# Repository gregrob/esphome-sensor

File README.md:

# ESPHome Sensor

An ESP32-S3 based sensor board system for ESPHome and Home Assistant, designed for outdoor environmental monitoring with a focus on hot water system and water tank level monitoring. Includes a complete mechanical system with 3D printable parts and a purpose-built outdoor 12V DC power distribution unit.

*Tank Sensor with Adapter*

*Tank Sensor in Operation*

## Features

- ESP32-S3 (FeatherS3D) with WiFi and ESPHome integration
- PiicoDev OLED display for local status indication
- Dual 1-Wire buses for DS18B20 temperature sensors
- I2C expansion for ToF distance sensors (DFRobot SEN0590)
- RGB LED status indicator with gradient colour coding
- Outdoor-rated polycarbonate enclosures with cable glands
- Purpose-built 12V DC zone power distribution unit (PSU backboard)
- 3D printed PETG-HF mechanical components

## Main Hardware Overview

| Component | Description |
|-----------|-------------|
| ESP32-S3 FeatherS3D | Main microcontroller |
| PiicoDev OLED 128x64 | Local display |
| Pololu D24V5F5 | 5V step-down regulator |
| DFRobot SEN0590 | ToF distance sensor |
| DS18B20 | 1-Wire temperature sensors |
| Mean Well IRM-30-12ST | 12V 2.5A AC/DC PSU |

## Documentation

- [Hardware](docs/hardware.md) — PCB design, schematic, BOM, KiCad files
- [Mechanical](docs/mechanical.md) — 3D printing, enclosures, print settings, materials
- [PSU Backboard](docs/esphome-sensor-psu-backboard.md) — Outdoor 12V DC power distribution unit

## Project Structure

```
├── README.md
├── hardware/
│   └── kicad/              # KiCad schematic, PCB, Gerber, BOM
├── mechanical/
│   ├── fusion360/          # Fusion 360 source files (.f3d)
│   ├── exports/            # STL and STEP files for printing
│   └── icons/              # Incons used in the covers
├── datasheets/             # Component datasheets
└── docs/                   # Detailed documentation
    └── images/             # Build photos
```

## Applications

- Heat pump hot water system monitoring (temperature, capacity estimation)
- Rainwater tank level monitoring (ToF distance sensor)
- Outdoor distributed IoT sensor power distribution

## TODO

- [ ] Write `docs/hardware.md`
- [ ] Write `docs/mechanical.md`
- [ ] Better tank sensor demo photo
- [ ] Sync software for ESPHome in personal HA repo here
- [ ] UV rated cables for ToF sensor
- [ ] Finalise tank adaptr
  - [ ] Proper cable mounts
  - [ ] Brass inserts
  - [ ] Exit hole size increase
- [ ] Inprove 3D printed covers in PETG-HF
  - [ ] Document the improvement - 8 top layers, Hilbery Curve top surface, Gyroid infill, top surface speed 35 mm/s
- [ ] Move algorithm to device for the hws sensor
- [ ] Possibly 3D print UV shroud for devices
- [ ] Light pipes on the tank sensor

## License

MIT License — Copyright (c) 2026 Greg Robinson

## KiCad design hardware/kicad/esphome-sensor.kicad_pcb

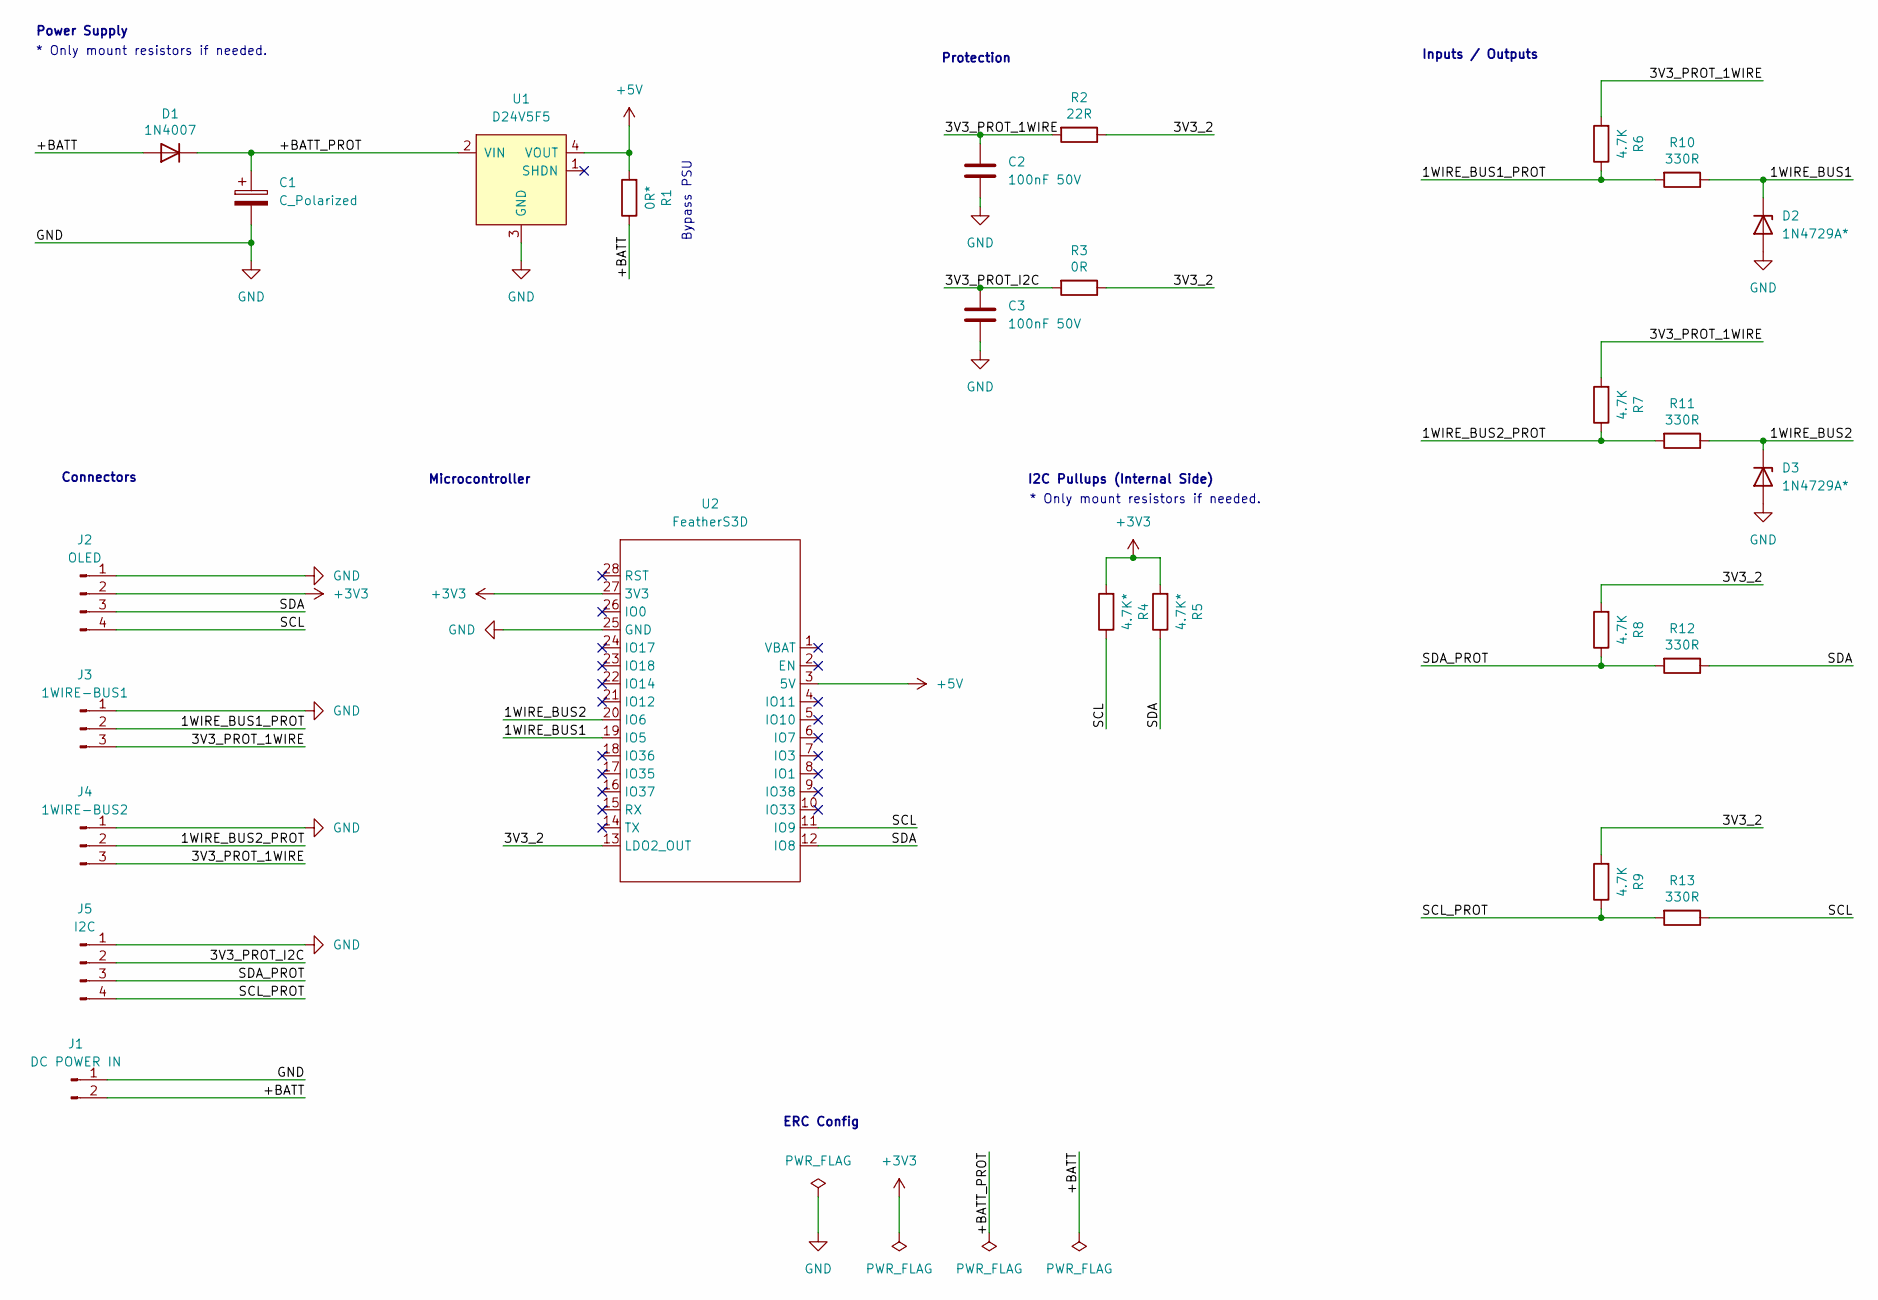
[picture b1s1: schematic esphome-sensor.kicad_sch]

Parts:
C1: C_Polarized; CP_Radial_D8.0mm_P3.50mm
C2, C3: 100nF 50V; C_Disc_D5.0mm_W2.5mm_P5.00mm
D1: 1N4007; D_DO-41_SOD81_P10.16mm_Horizontal
D2, D3: 1N4729A*; D_DO-41_SOD81_P10.16mm_Horizontal
J1: DC POWER IN; TerminalBlock_Phoenix_PT-1,5-2-5.0-H_1x02_P5.00mm_Horizontal
J2: OLED; PiicoDev_OLED_Module
J3: 1WIRE-BUS1; TerminalBlock_Phoenix_PT-1,5-3-5.0-H_1x03_P5.00mm_Horizontal
J4: 1WIRE-BUS2; TerminalBlock_Phoenix_PT-1,5-3-5.0-H_1x03_P5.00mm_Horizontal
J5: I2C; TerminalBlock_Phoenix_PT-1,5-4-5.0-H_1x04_P5.00mm_Horizontal
R1: 0R*; R_Axial_DIN0207_L6.3mm_D2.5mm_P10.16mm_Horizontal
R2: 22R; R_Axial_DIN0207_L6.3mm_D2.5mm_P10.16mm_Horizontal
R3: 0R; R_Axial_DIN0207_L6.3mm_D2.5mm_P10.16mm_Horizontal
R4, R5: 4.7K*; R_Axial_DIN0207_L6.3mm_D2.5mm_P10.16mm_Horizontal
R6, R7, R8, R9: 4.7K; R_Axial_DIN0207_L6.3mm_D2.5mm_P10.16mm_Horizontal
R10, R11, R12, R13: 330R; R_Axial_DIN0207_L6.3mm_D2.5mm_P10.16mm_Horizontal
U1: D24V5F5
U2: FeatherS3D

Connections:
+3V3: J2.2, R4.2, R5.2, U2.27 (3V3)
+5V: R1.2, U1.4 (VOUT), U2.3 (5V)
/1WIRE_BUS1: D2.1 (K), R10.1, U2.19 (IO5)
/1WIRE_BUS1_PROT: J3.2, R6.1, R10.2
/1WIRE_BUS2: D3.1 (K), R11.1, U2.20 (IO6)
/1WIRE_BUS2_PROT: J4.2, R7.1, R11.2
/3V3_2: R2.1, R3.1, R8.2, R9.2, U2.13 (LDO2_OUT)
/3V3_PROT_1WIRE: C2.1, J3.3, J4.3, R2.2, R6.2, R7.2
/3V3_PROT_I2C: C3.1, J5.2, R3.2
/+BATT: D1.2 (A), J1.2, R1.1
/+BATT_PROT: C1.1, D1.1 (K), U1.2 (VIN)
/SCL: J2.4, R4.1, R13.1, U2.11 (IO9)
/SCL_PROT: J5.4, R9.1, R13.2
/SDA: J2.3, R5.1, R12.1, U2.12 (IO8)
/SDA_PROT: J5.3, R8.1, R12.2
GND: C1.2, C2.2, C3.2, D2.2 (A), D3.2 (A), J1.1, J2.1, J3.1, J4.1, J5.1, U1.3 (GND), U2.25 (GND)

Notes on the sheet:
ERC Config
Connectors
I2C Pullups (Internal Side)
* Only mount resistors if needed.
Inputs / Outputs
Bypass PSU
Microcontroller
Protection
Power Supply

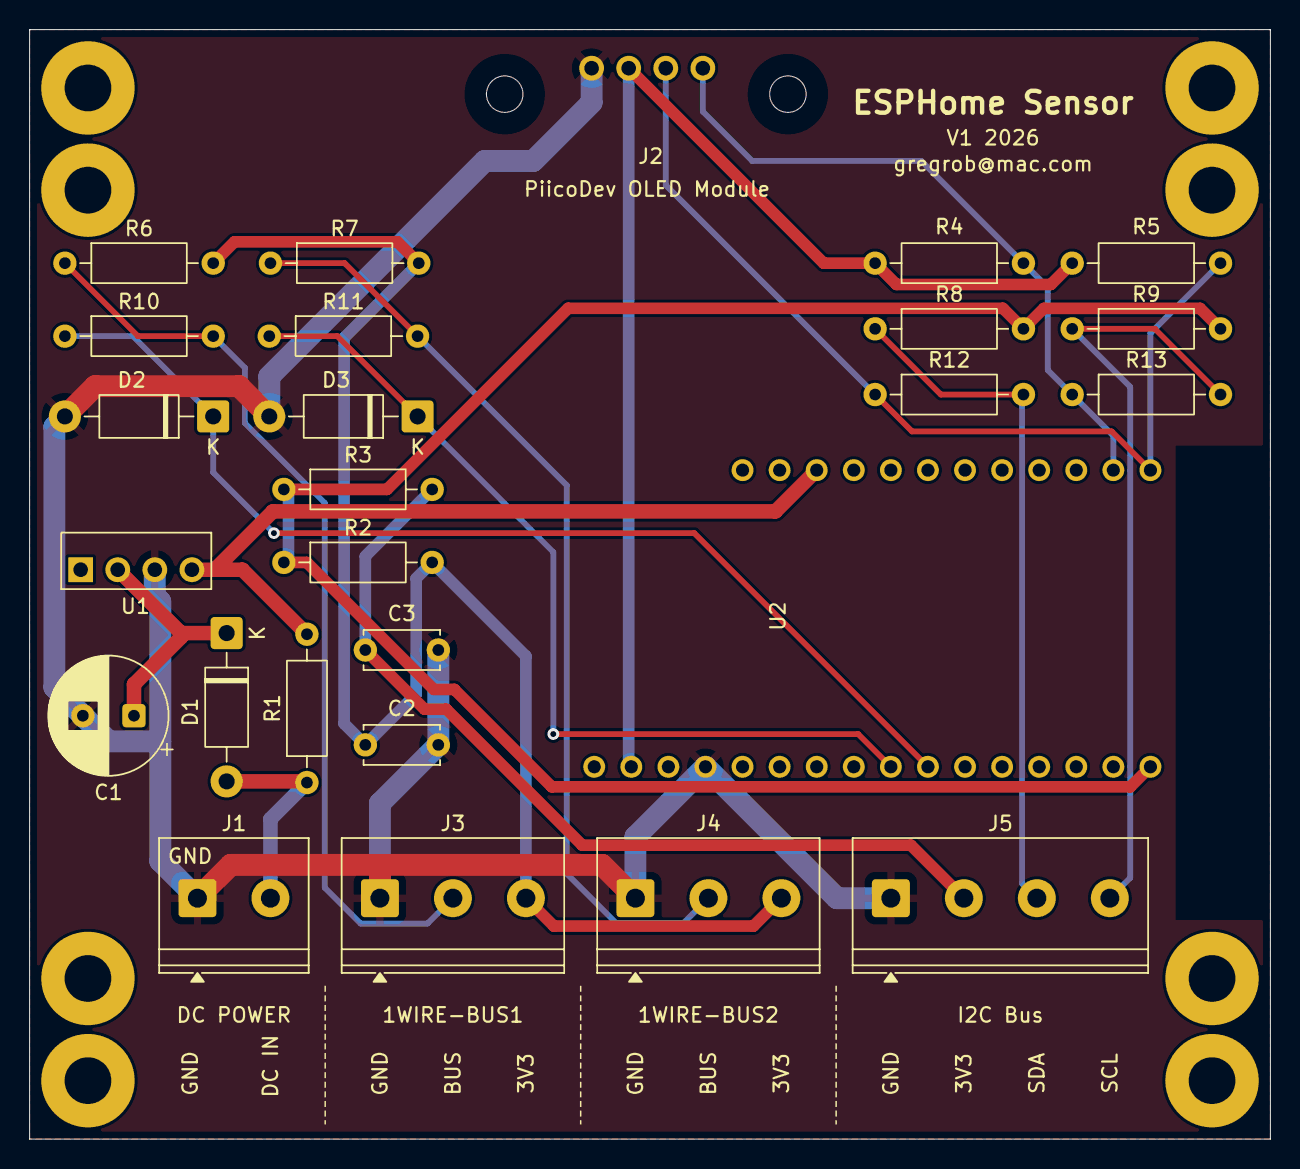
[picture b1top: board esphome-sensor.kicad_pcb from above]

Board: 2 copper layers, 85.0 x 76.0 mm, 34 parts (0 on the bottom side), 16 nets.

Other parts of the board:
H1, H2, H3, H4, H5, H6, H7, H8: MountingHole_3.2mm_M3_Pad

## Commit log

2026-02-24 initial version of hardware
2026-02-24 step exports for pcb and cover
2026-02-24 added export of fusion 360 cover
2026-02-26 filter cap defined
2026-02-26 initial BOM
2026-03-05 schematic pdf and bom
2026-03-17 final proposal for top cover with 2x LED's and icons
2026-03-17 plot directory set
2026-04-23 start of psu build
2026-04-25 add PSU backboard documentation with design, print settings, and assembly notes
2026-04-25 refine PSU backboard documentation with detailed design specifications, print settings, and assembly instructions
2026-04-25 update PSU backboard documentation with direct links to hardware sources
2026-04-25 add new STL files for PSU backboard and fuse holder, and update Fusion 360 model
2026-04-25 add HM3194 datasheet with technical specifications and dimensions
2026-04-25 add documentation for ESPHome Sensor PSU backboard including design, print settings, and assembly instructions
2026-05-03 add new STL and Fusion 360 files for ESPHome sensor tank adapter
2026-05-03 add images and documentation for PSU backboard assembly and features
2026-05-04 refactored pcb cover
2026-05-04 icon for water
2026-05-04 tank pcb cover added
2026-05-05 add initial README.md with project overview and documentation structure
2026-05-05 add tank sensor demo photo to README and update feature list
2026-05-05 parameters for best quality 3d printed covers with embossing
2026-05-06 update README.md with new todo's
2026-05-06 add tank sensor operation image to README
